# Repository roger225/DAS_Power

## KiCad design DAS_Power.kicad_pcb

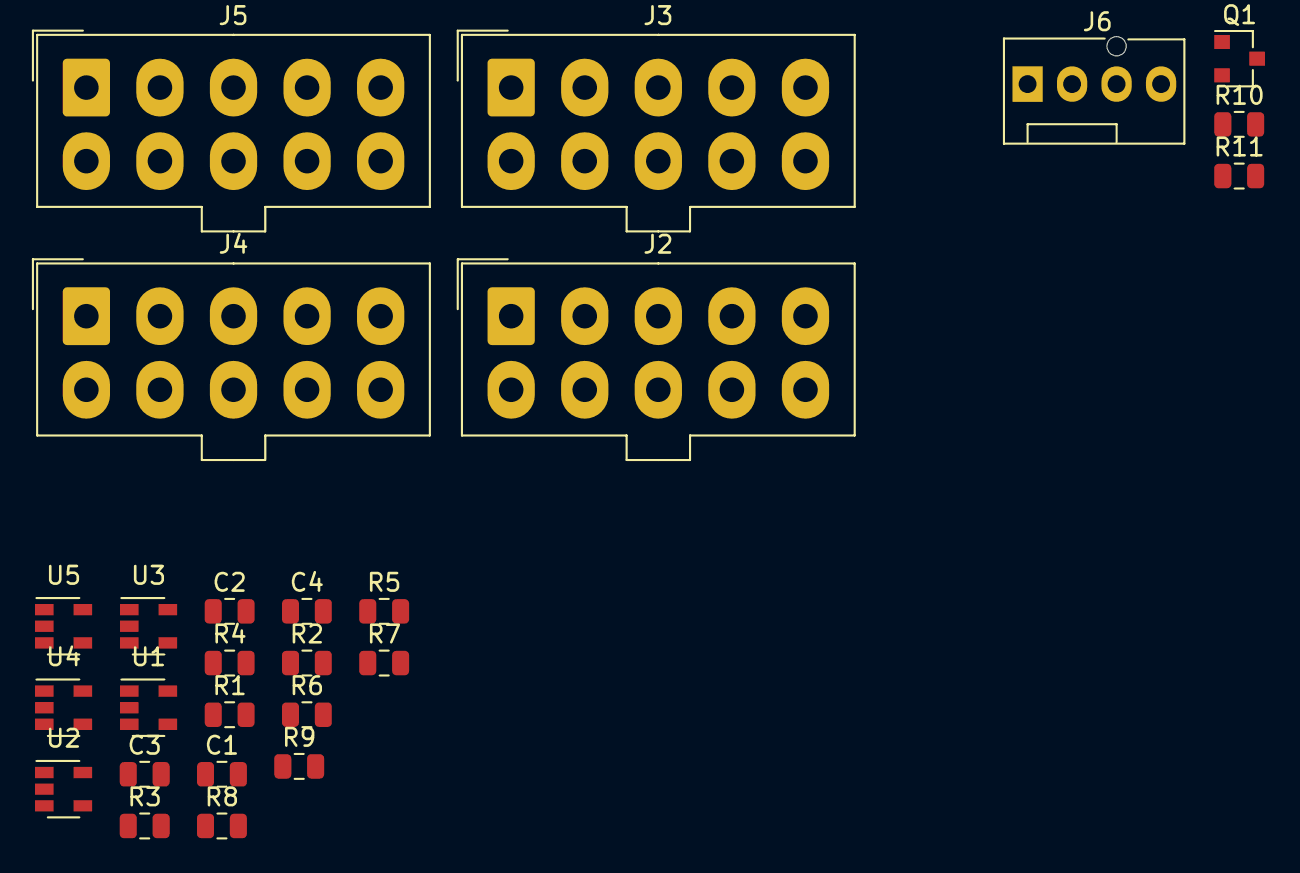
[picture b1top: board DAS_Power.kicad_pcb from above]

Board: 2 copper layers, 26 parts (0 on the bottom side), 14 nets, no tracks yet.

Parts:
C1, C2, C3, C4: 0.1uf; C_0805_2012Metric
J2, J3, J4, J5: Conn_02x05_Top_Bottom; Molex_Mini-Fit_Jr_87427-1042_2x05_P4.20mm_Vertical
J6: Conn_01x04; FanPinHeader_1x04_P2.54mm_Vertical
Q1: 2N7002; SOT-23
R1, R3, R6, R8, R11: 10K; R_0805_2012Metric
R2, R4, R7, R9: 3.3K; R_0805_2012Metric
R5, R10: 4.7K; R_0805_2012Metric
U1, U2, U3, U4, U5: LM321; SOT-23-5

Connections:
+3V3: C1.1, C2.1, C3.1, C4.1, U1.5, U2.5, U3.5, U4.5, U5.5
+5V_BUS: J2.8, J2.9, J3.8, J3.9, J4.8, J4.9, J5.8, J5.9, R6.1, R10.1
+12V_BUS: J2.5, J2.6, J2.7, J2.10, J3.5, J3.6, J3.7, J3.10, J4.5, J4.6, J4.7, J4.10, J5.5, J5.6, J5.7, J5.10, J6.2, R8.1
/ADC/+5V_BUS_ADC_OUT: U4.3, U4.4
/ADC/+5V_IN_ADC_OUT: U2.3, U2.4
/ADC/+12V_BUS_ADC_OUT: U5.3, U5.4
/ADC/+12V_IN_ADC_OUT: U3.3, U3.4
GND: C1.2, C2.2, C3.2, C4.2, J2.1, J2.2, J2.3, J2.4, J3.1, J3.2, J3.3, J3.4, J4.1, J4.2, J4.3, J4.4, J5.1, J5.2, J5.3, J5.4, J6.1, Q1.2, R2.2, R4.2, R7.2, R9.2, R11.2, U1.2, U2.2, U3.2, U4.2, U5.2
unnamed: J6.4, Q1.3, R10.2
unnamed: Q1.1, R11.1
unnamed: R1.2, R2.1, U2.1
unnamed: R3.2, R4.1, U3.1
unnamed: R6.2, R7.1, U4.1
unnamed: R8.2, R9.1, U5.1

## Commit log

2020-01-28 init
2020-01-28 adc finish v1
2020-01-28 add hierarchical pin
2020-01-28 pause at power input
2020-01-29 addgit ignopre
2020-01-29 .gitignore fix
2020-01-29 resistor symbol modify
2020-01-29 fac pmw v1
2020-01-29 add pdf 3d for old design
2020-01-30 add some capacitor in fan and power_out
2020-01-30 add power_or sheet
2020-01-30 add ina139
2020-02-02 add 0.5mR R2725
2020-02-02 3.3v LDO power
2020-02-02 pause on power or
2020-02-02 pause at power or
2020-02-08 move out the current sensor frome power switch
2020-02-08 currentsensor v1
2020-02-08 power or switch v1
